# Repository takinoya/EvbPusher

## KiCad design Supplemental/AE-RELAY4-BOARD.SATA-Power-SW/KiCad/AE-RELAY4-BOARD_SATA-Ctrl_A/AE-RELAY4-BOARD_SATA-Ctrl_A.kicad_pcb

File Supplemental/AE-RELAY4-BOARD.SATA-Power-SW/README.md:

[English](README.md) | [Japanese](README.ja.md)
----

# SFX Power Complex

TBD
\(Original is here ==> [Japanese](README.ja.md)\)

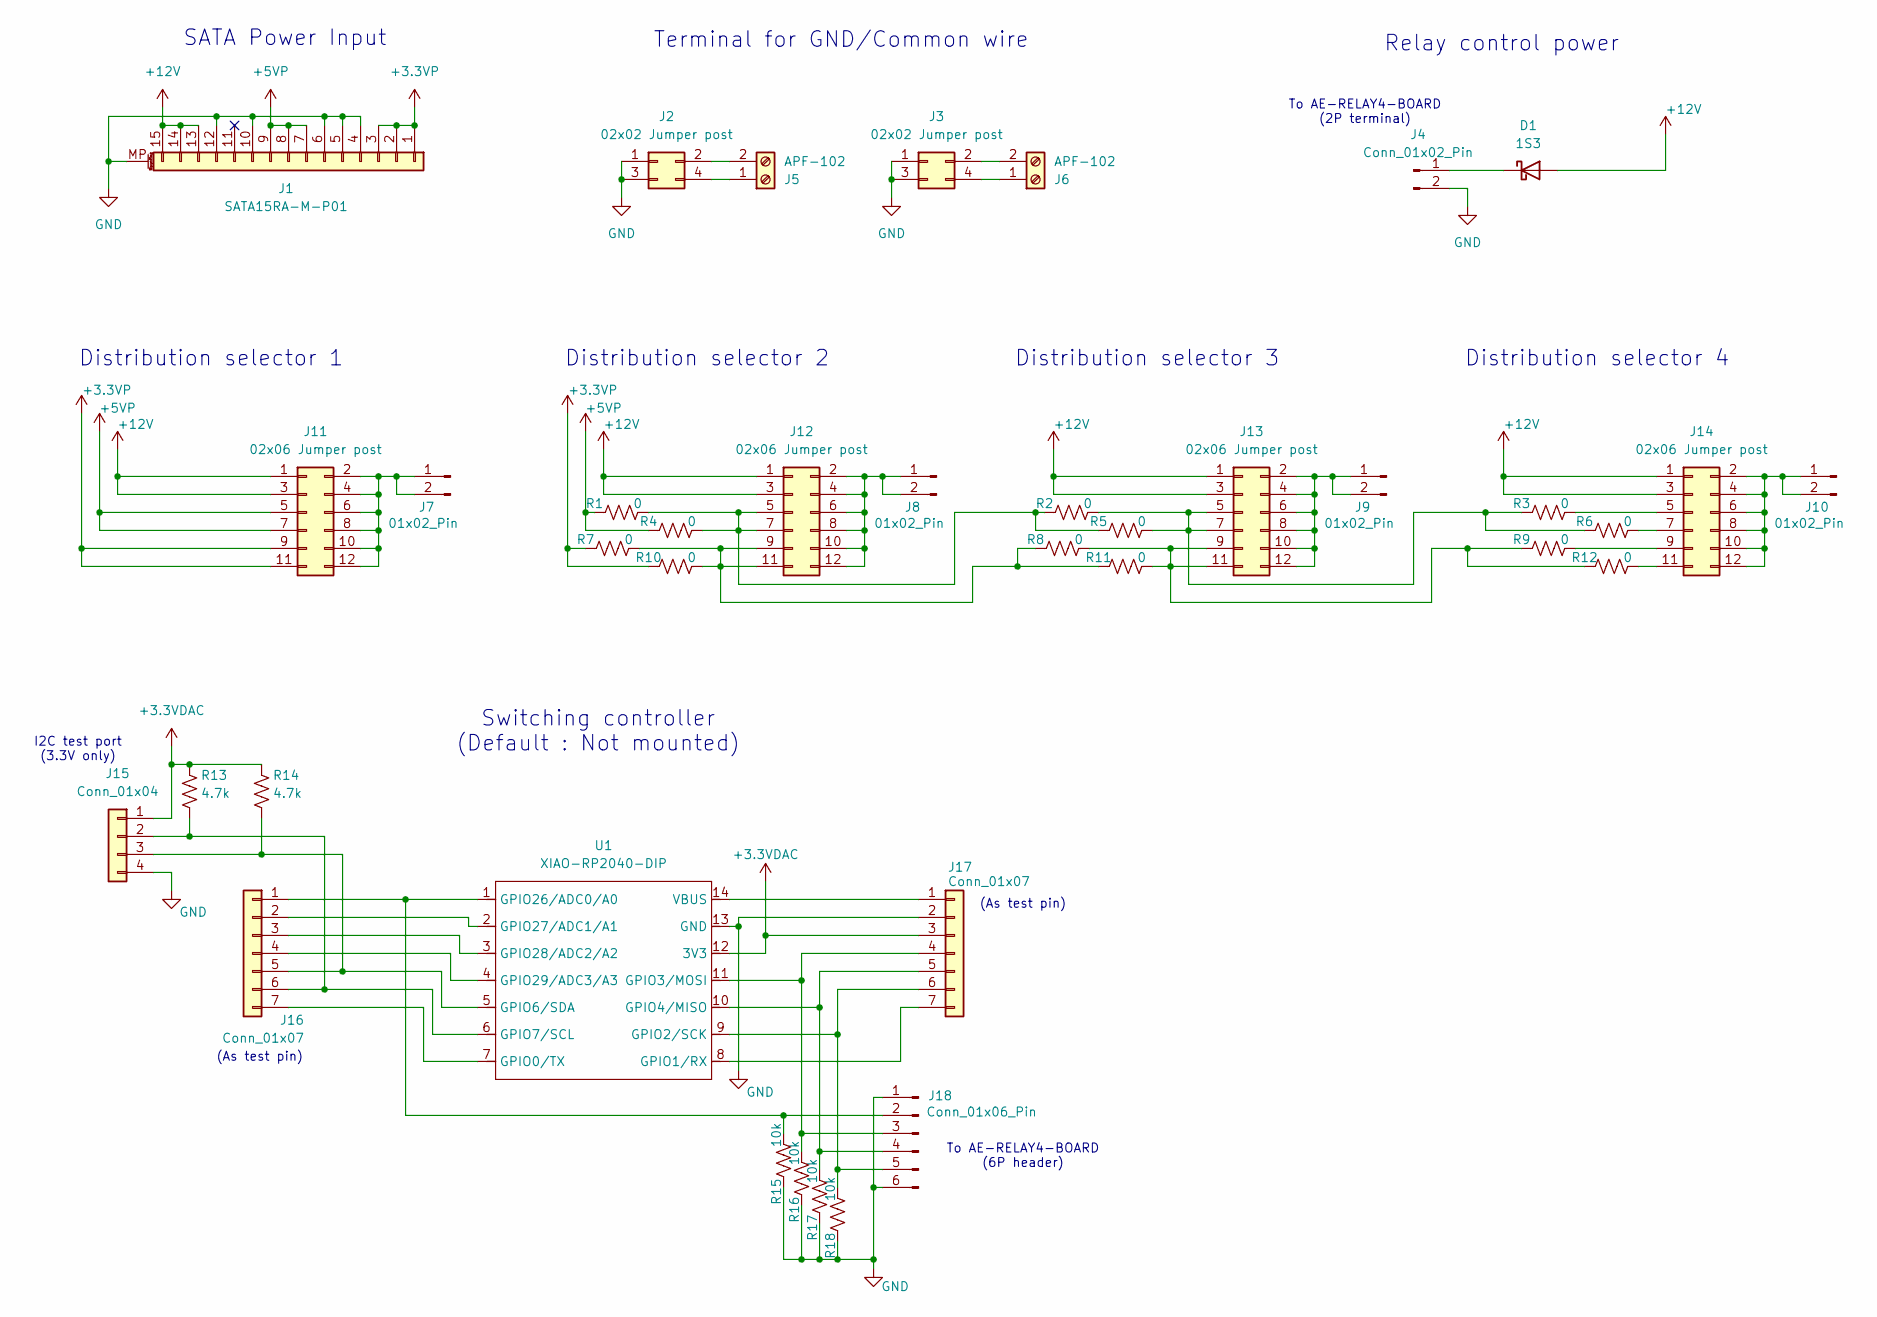
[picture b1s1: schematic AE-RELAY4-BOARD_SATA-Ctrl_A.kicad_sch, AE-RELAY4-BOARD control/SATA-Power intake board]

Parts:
D1: 1S3; D_DO-35_SOD27_P7.62mm_Horizontal
J1: SATA15RA-M-P01; SATA15RA-M-P01_Vertical_TOSA
J2, J3: 02x02 Jumper post; PinHeader_2x02_P2.54mm_nomargin_Vertical_TOSA
J4: Conn_01x02_Pin; PinHeader_1x02_P2.54mm_nomargin_Vertical_TOSA
J5, J6: APF-102; TerminalBlock_Phoenix_APF-102_1x02_P5.08mm_Horizontal
J7, J8, J9, J10: 01x02_Pin; PinHeader_1x02_P2.54mm_nomargin_Vertical_TOSA
J11, J12, J13, J14: 02x06 Jumper post; PinHeader_2x06_P2.54mm_nomargin_Vertical_TOSA
J15: Conn_01x04; PinHeader_1x04_P2.54mm_Vertical
J16, J17: Conn_01x07; PinHeader_1x07_P2.54mm_nomargin_Vertical_TOSA
J18: Conn_01x06_Pin; PinHeader_1x06_P2.54mm_Horizontal
R1, R2, R3, R4, R5, R6, R7, R8, R9, R10, R11, R12: 0; R_Axial_DIN0207_L6.3mm_D2.5mm_P10.16mm_Horizontal_TOSA
R13, R14: 4.7k; R_Axial_DIN0207_L6.3mm_D2.5mm_P2.54mm_Vertical_TOSA
R15, R16, R17, R18: 10k; R_Axial_DIN0207_L6.3mm_D2.5mm_P7.62mm_Horizontal_TOSA
U1: XIAO-RP2040-DIP

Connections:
+3.3VDAC: J15.1, J17.3, R13.1, R14.1, U1.12 (3V3)
+3.3VP: J1.1, J1.2, J1.3, J11.9, J11.11, R7.1, R10.1
+5VP: J1.7, J1.8, J1.9, J11.5, J11.7, R1.1, R4.1
+12V: D1.2 (A), J1.13, J1.14, J1.15, J11.1, J11.3, J12.1, J12.3, J13.1, J13.3, J14.1, J14.3
GND: J1.4, J1.5, J1.6, J1.10, J1.12, J1.MP (MountPin), J2.1, J2.3, J3.1, J3.3, J4.2, J15.4, J17.2, J18.1, J18.6, R15.2, R16.2, R17.2, R18.2, U1.13 (GND)
unnamed: D1.1 (K), J4.1
unnamed: J2.2, J5.2
unnamed: J2.4, J5.1
unnamed: J3.2, J6.2
unnamed: J3.4, J6.1
unnamed: J10.1, J10.2, J14.2, J14.4, J14.6, J14.8, J14.10, J14.12
unnamed: J7.1, J7.2, J11.2, J11.4, J11.6, J11.8, J11.10, J11.12
unnamed: J12.5, J12.7, R1.2, R2.1, R4.2, R5.1
unnamed: J8.1, J8.2, J12.2, J12.4, J12.6, J12.8, J12.10, J12.12
unnamed: J12.9, J12.11, R7.2, R8.1, R10.2, R11.1
unnamed: J13.5, J13.7, R2.2, R3.1, R5.2, R6.1
unnamed: J9.1, J9.2, J13.2, J13.4, J13.6, J13.8, J13.10, J13.12
unnamed: J13.9, J13.11, R8.2, R9.1, R11.2, R12.1
unnamed: J14.5, R3.2
unnamed: J14.7, R6.2
unnamed: J14.9, R9.2
unnamed: J14.11, R12.2
unnamed: J15.2, J16.6, R13.2, U1.6 (GPIO7/SCL)
unnamed: J15.3, J16.5, R14.2, U1.5 (GPIO6/SDA)
unnamed: J16.1, J18.2, R15.1, U1.1 (GPIO26/ADC0/A0)
unnamed: J16.2, U1.2 (GPIO27/ADC1/A1)
unnamed: J16.3, U1.3 (GPIO28/ADC2/A2)
unnamed: J16.4, U1.4 (GPIO29/ADC3/A3)
unnamed: J16.7, U1.7 (GPIO0/TX)
unnamed: J17.1, U1.14 (VBUS)
unnamed: J17.4, J18.3, R16.1, U1.11 (GPIO3/MOSI)
unnamed: J17.5, J18.4, R17.1, U1.10 (GPIO4/MISO)
unnamed: J17.6, J18.5, R18.1, U1.9 (GPIO2/SCK)
unnamed: J17.7, U1.8 (GPIO1/RX)

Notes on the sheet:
To AE-RELAY4-BOARD (6P header)
Distribution selector 4
Distribution selector 1
To AE-RELAY4-BOARD (2P terminal)
Relay control power
(As test pin)
Terminal for GND/Common wire
Switching controller (Default : Not mounted)
Distribution selector 2
Distribution selector 3
I2C test port (3.3V only)
SATA Power Input

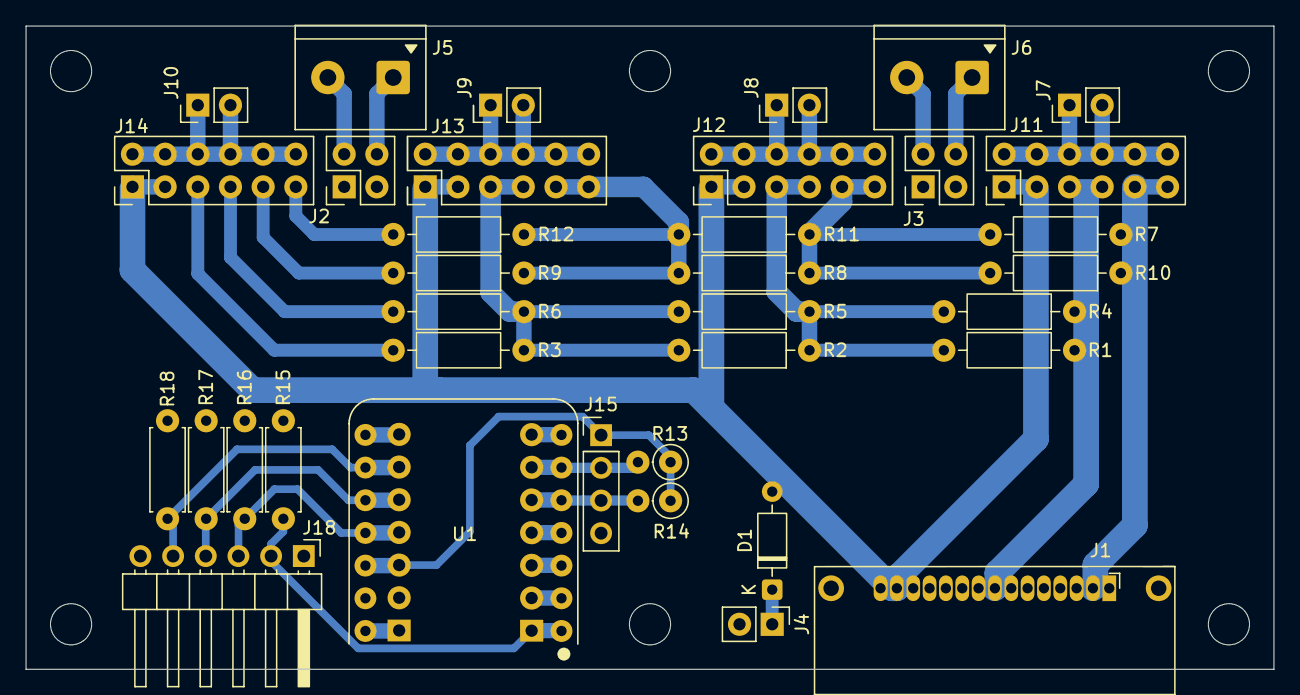
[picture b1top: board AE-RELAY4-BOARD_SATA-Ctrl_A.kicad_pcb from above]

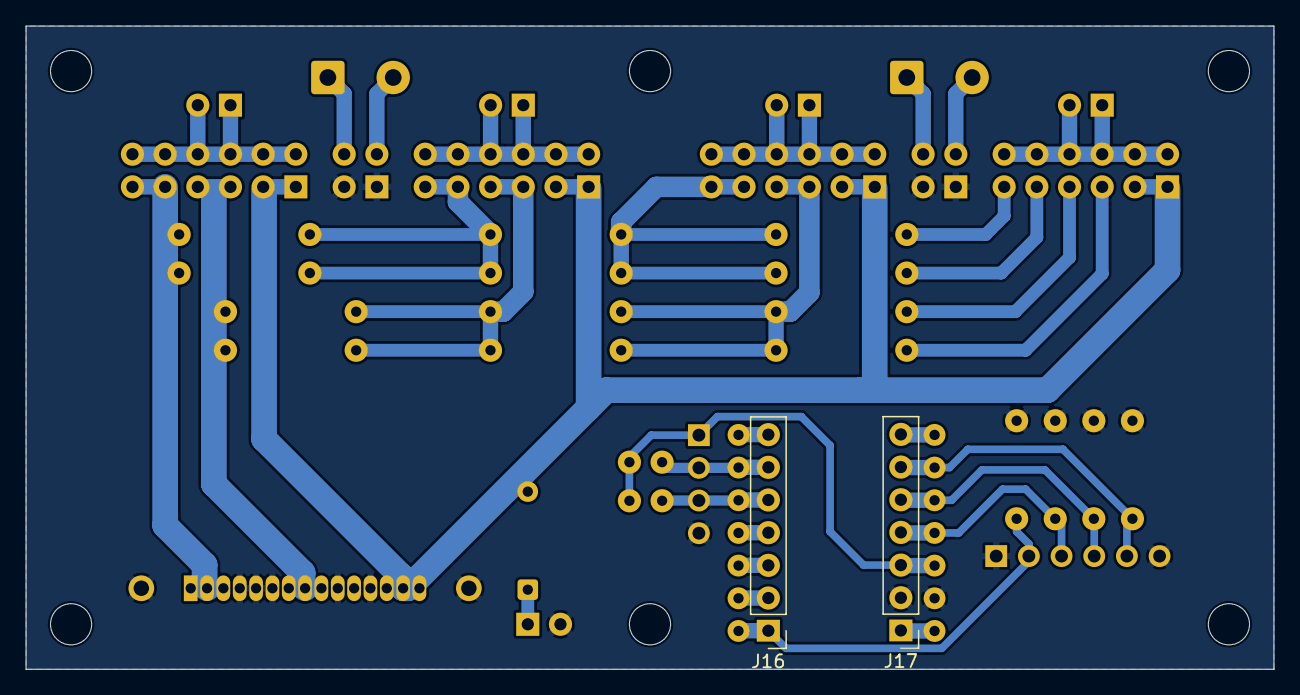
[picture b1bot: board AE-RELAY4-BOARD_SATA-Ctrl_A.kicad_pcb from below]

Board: 2 copper layers, 97.0 x 50.0 mm, 44 parts (2 on the bottom side), 34 nets.

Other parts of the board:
MH1, MH1#2, MH1#3, MH1#4, MH1#5, MH1#6: MountingHole_3.2mm_M3

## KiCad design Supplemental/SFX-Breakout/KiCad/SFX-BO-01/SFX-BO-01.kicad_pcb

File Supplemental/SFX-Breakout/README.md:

[English](README.md) | [Japanese](README.ja.md)
----

# SFX Breakout board

TBD
\(Original is here ==> [Japanese](README.ja.md)\)

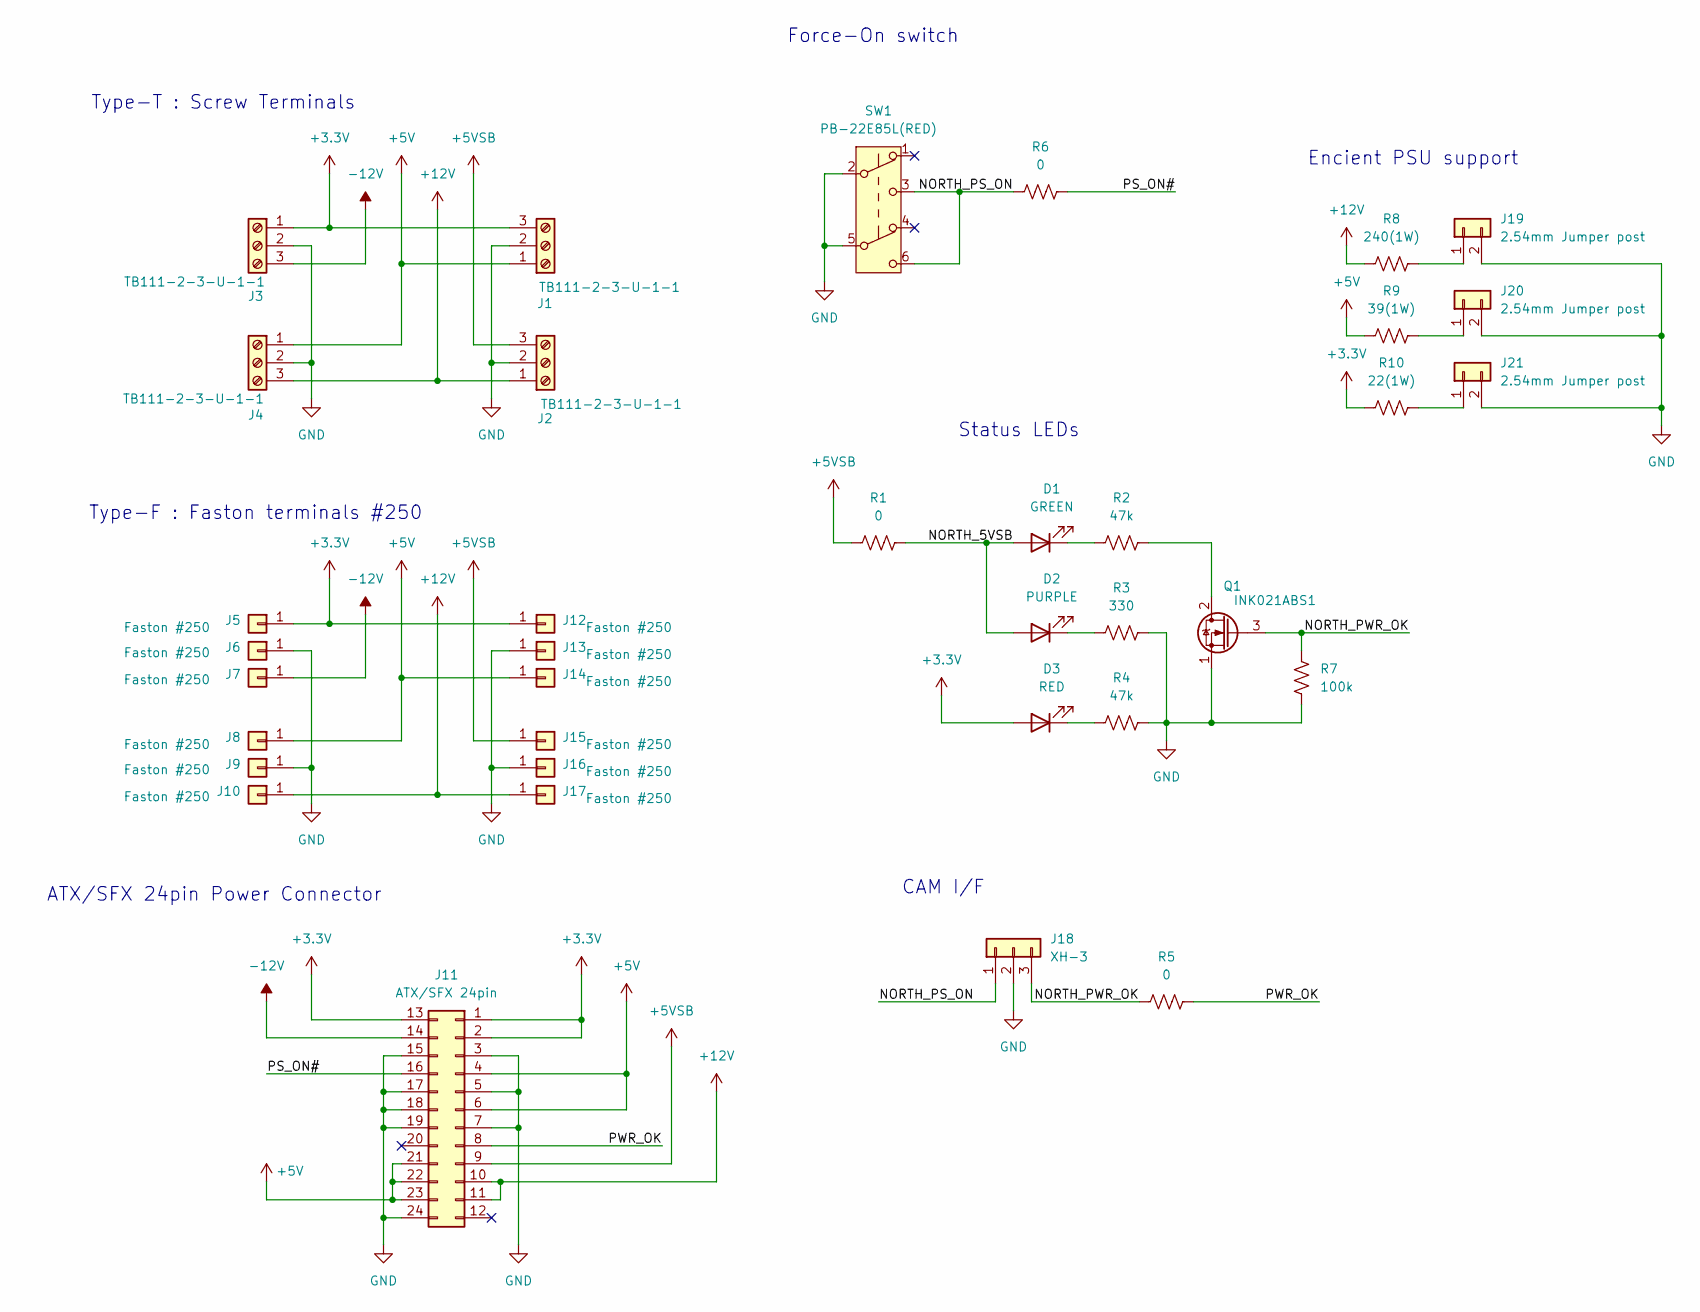
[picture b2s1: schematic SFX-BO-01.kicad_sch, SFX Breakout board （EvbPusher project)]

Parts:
D1: GREEN; LED_D3.0mm
D2: PURPLE; LED_D3.0mm
D3: RED; LED_D3.0mm
J1, J2, J3, J4: TB111-2-3-U-1-1; TerminalBlock_Alphaplus_TB111-2-3-U-1-1_1x03_P5.08mm_Horizo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
J5, J6, J7, J8, J9, J10, J12, J13, J14, J15, J16, J17: Faston #250; Faston_PC250
J11: ATX/SFX 24pin; Molex_Mini-Fit_Jr_5566-24A_2x12_P4.20mm_Vertical
J18: XH-3; JST_XH_B3B-XH-A_1x03_P2.50mm_Vertical
J19, J20, J21: 2.54mm Jumper post; PinHeader_1x02_P2.54mm_nomargin_Vertical
Q1: INK021ABS1; TO-92S_Wide_TMVC
R1, R5, R6: 0; R_Axial_DIN0207_L6.3mm_D2.5mm_P15.24mm_Horizontal_TOSA
R2, R4: 47k; R_Axial_DIN0207_L6.3mm_D2.5mm_P2.54mm_Vertical_TOSA
R3: 330; R_Axial_DIN0207_L6.3mm_D2.5mm_P2.54mm_Vertical_TOSA
R7: 100k; R_Axial_DIN0207_L6.3mm_D2.5mm_P2.54mm_Vertical_TOSA
R8: 240(1W); R_Axial_DIN0207_L6.3mm_D2.5mm_P2.54mm_Vertical_TOSA
R9: 39(1W); R_Axial_DIN0207_L6.3mm_D2.5mm_P2.54mm_Vertical_TOSA
R10: 22(1W); R_Axial_DIN0207_L6.3mm_D2.5mm_P2.54mm_Vertical_TOSA
SW1: PB-22E85L(RED); SW_Push_2P2T_Toggle_PB-22E85L

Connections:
+3.3V: D3.2 (A), J1.3, J3.1, J5.1, J11.1, J11.2, J11.13, J12.1, R10.1
+5V: J1.1, J4.1, J8.1, J11.4, J11.6, J11.21, J11.22, J11.23, J14.1, R9.1
+5VSB: J2.3, J11.9, J15.1, R1.1
+12V: J2.1, J4.3, J10.1, J11.10, J11.11, J17.1, R8.1
-12V: J3.3, J7.1, J11.14
/NORTH_5VSB: D1.2 (A), D2.2 (A), R1.2
/NORTH_PS_ON: J18.1, R6.1, SW1.3 (C), SW1.6 (C)
/NORTH_PWR_OK: J18.3, Q1.3 (G), R5.1, R7.2
/PS_ON#: J11.16, R6.2
/PWR_OK: J11.8, R5.2
GND: J1.2, J2.2, J3.2, J4.2, J6.1, J9.1, J11.3, J11.5, J11.7, J11.15, J11.17, J11.18, J11.19, J11.24, J13.1, J16.1, J18.2, J19.2, J20.2, J21.2, Q1.1 (S), R3.2, R4.2, R7.1, SW1.2 (B), SW1.5 (B)
unnamed: D1.1 (K), R2.1
unnamed: D2.1 (K), R3.1
unnamed: D3.1 (K), R4.1
unnamed: J19.1, R8.2
unnamed: J20.1, R9.2
unnamed: J21.1, R10.2
unnamed: Q1.2 (D), R2.2

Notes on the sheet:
Type-T : Screw Terminals
CAM I/F
ATX/SFX 24pin Power Connector
Status LEDs
Encient PSU support
Type-F : Faston terminals #250
Force-On switch

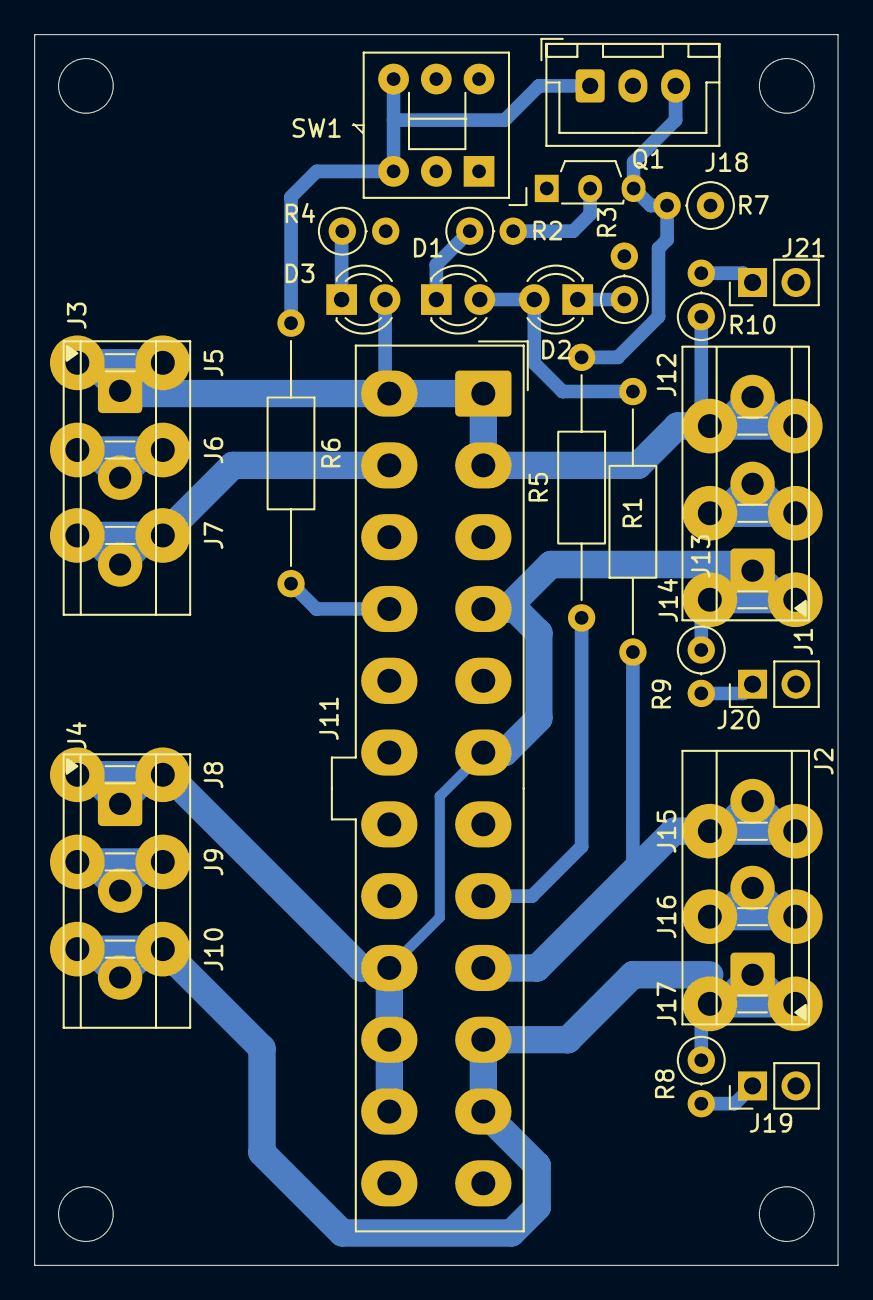
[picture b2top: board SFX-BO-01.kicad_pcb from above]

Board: 2 copper layers, 47.0 x 72.0 mm, 40 parts (0 on the bottom side), 18 nets.

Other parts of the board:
MH1, MH2, MH3, MH4: MountingHole_3.2mm_M3

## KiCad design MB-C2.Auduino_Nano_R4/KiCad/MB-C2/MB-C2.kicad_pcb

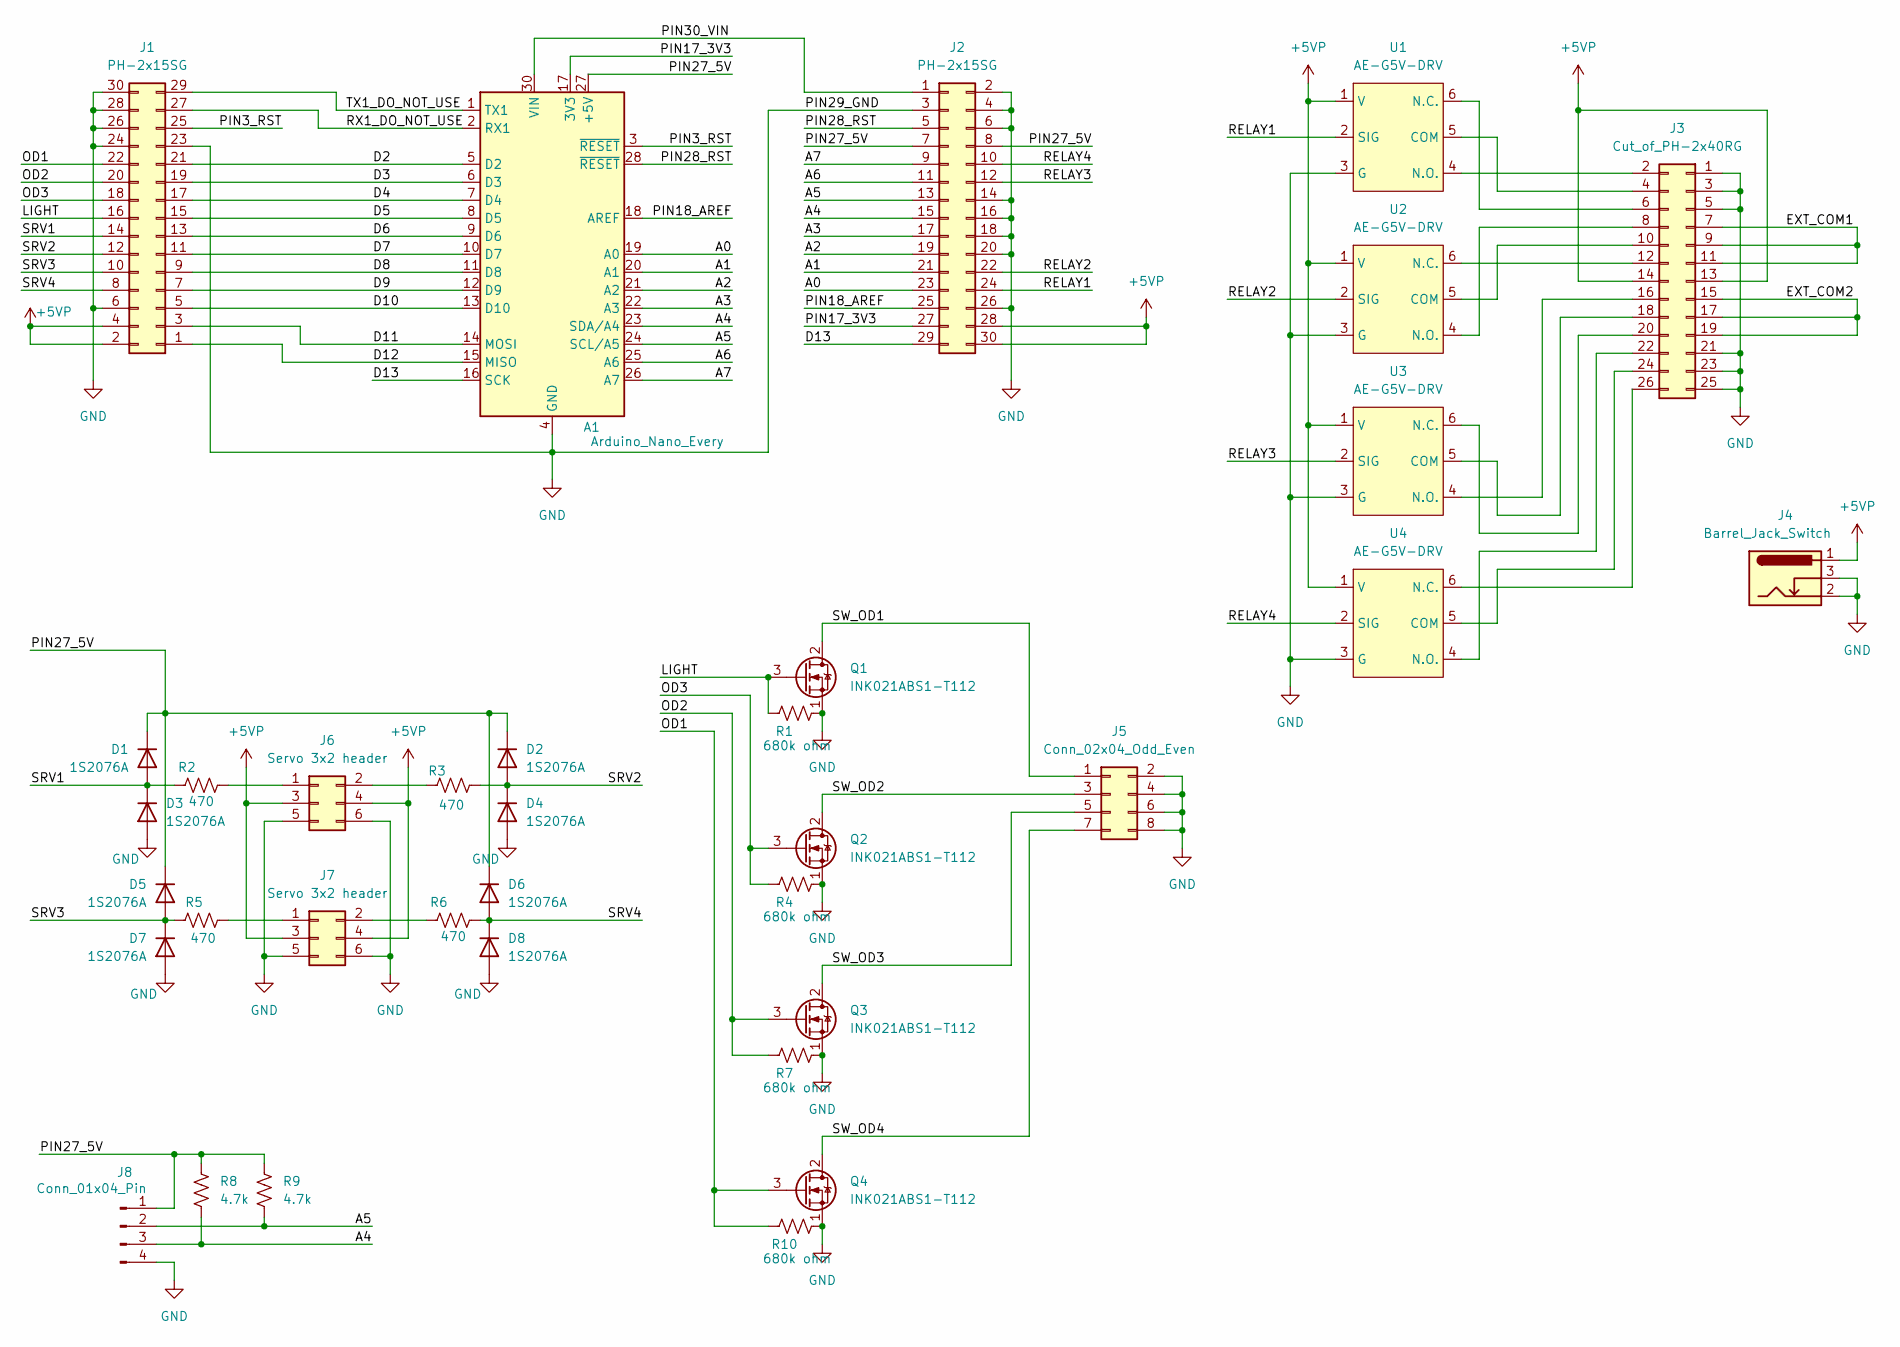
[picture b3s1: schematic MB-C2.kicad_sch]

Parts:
A1: Arduino_Nano_Every; Arduino_Nano__silk_tune
D1, D2, D3, D4, D5, D6, D7, D8: 1S2076A; D_DO-34_SOD68_P2.54mm_Vertical_KathodeUp
J1, J2: PH-2x15SG; PinHeader_2x15_P2.54mm_Vertical
J3: Cut_of_PH-2x40RG; PinHeader_2x13_P2.54mm_Vertical
J4: Barrel_Jack_Switch; BarrelJack_2.1mm_4A_18742_TMVC
J5: Conn_02x04_Odd_Even; PinHeader_2x04_P2.54mm_nomargin_Vertical
J6, J7: Servo 3x2 header; PinHeader_2x03_P2.54mm_nomargin_Vertical
J8: Conn_01x04_Pin; PinHeader_1x04_P2.54mm_Vertical
Q1, Q2, Q3, Q4: INK021ABS1-T112; TO-92S_Wide_TMVC
R1, R4, R7, R10: 680k ohm; R_Axial_DIN0204_L3.6mm_D1.6mm_P2.54mm_Vertical
R2, R5: 470; R_Axial_DIN0204_L3.6mm_D1.6mm_P5.08mm_Horizontal
R3, R6: 470; R_Axial_DIN0204_L3.6mm_D1.6mm_P2.54mm_Vertical
R8, R9: 4.7k; R_Axial_DIN0204_L3.6mm_D1.6mm_P7.62mm_Horizontal_TMVC
U1, U2, U3, U4: AE-G5V-DRV

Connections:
+5VP: J1.2, J1.4, J2.28, J2.30, J3.13, J3.14, J4.1, J6.3, J6.4, J7.3, J7.4, U1.1 (V), U2.1 (V), U3.1 (V), U4.1 (V)
/A0: A1.19 (A0), J2.23
/A1: A1.20 (A1), J2.21
/A2: A1.21 (A2), J2.19
/A3: A1.22 (A3), J2.17
/A4: A1.23 (SDA/A4), J2.15, J8.3, R8.2
/A5: A1.24 (SCL/A5), J2.13, J8.2, R9.2
/A6: A1.25 (A6), J2.11
/A7: A1.26 (A7), J2.9
/D2: A1.5 (D2), J1.21
/D3: A1.6 (D3), J1.19
/D4: A1.7 (D4), J1.17
/D5: A1.8 (D5), J1.15
/D6: A1.9 (D6), J1.13
/D7: A1.10 (D7), J1.11
/D8: A1.11 (D8), J1.9
/D9: A1.12 (D9), J1.7
/D10: A1.13 (D10), J1.5
/D11: A1.14 (MOSI), J1.3
/D12: A1.15 (MISO), J1.1
/D13: A1.16 (SCK), J2.29
/EXT_COM1: J3.7, J3.9, J3.11
/EXT_COM2: J3.15, J3.17, J3.19
/LIGHT: J1.16, Q1.3 (G), R1.1
/OD1: J1.22, Q4.3 (G), R10.1
/OD2: J1.20, Q3.3 (G), R7.1
/OD3: J1.18, Q2.3 (G), R4.1
/PIN3_RST: A1.3 (~RESET), J1.25
/PIN17_3V3: A1.17 (3V3), J2.27
/PIN18_AREF: A1.18 (AREF), J2.25
/PIN27_5V: A1.27 (+5V), D1.1 (K), D2.1 (K), D5.1 (K), D6.1 (K), J2.7, J2.8, J8.1, R8.1, R9.1
/PIN28_RST: A1.28 (~RESET), J2.5
/PIN30_VIN: A1.30 (VIN), J2.1
/RELAY1: J2.24, U1.2 (SIG)
/RELAY2: J2.22, U2.2 (SIG)
/RELAY3: J2.12, U3.2 (SIG)
/RELAY4: J2.10, U4.2 (SIG)
/RX1_DO_NOT_USE: A1.2 (RX1), J1.27
/SRV1: D1.2 (A), D3.1 (K), J1.14, R2.1
/SRV2: D2.2 (A), D4.1 (K), J1.12, R3.2
/SRV3: D5.2 (A), D7.1 (K), J1.10, R5.1
/SRV4: D6.2 (A), D8.1 (K), J1.8, R6.2
/SW_OD1: J5.1, Q1.2 (D)
/SW_OD2: J5.3, Q2.2 (D)
/SW_OD3: J5.5, Q3.2 (D)
/SW_OD4: J5.7, Q4.2 (D)
/TX1_DO_NOT_USE: A1.1 (TX1), J1.29
GND: A1.4 (GND), A1.29 (GND), D3.2 (A), D4.2 (A), D7.2 (A), D8.2 (A), J1.6, J1.23, J1.24, J1.26, J1.28, J1.30, J2.2, J2.3, J2.4, J2.6, J2.14, J2.16, J2.18, J2.20, J2.26, J3.1, J3.3, J3.5, J3.21, J3.23, J3.25, J4.2, J4.3, J5.2, J5.4, J5.6, J5.8, J6.5, J6.6, J7.5, J7.6, J8.4, Q1.1 (S), Q2.1 (S), Q3.1 (S), Q4.1 (S), R1.2, R4.2, R7.2, R10.2, U1.3 (G), U2.3 (G), U3.3 (G), U4.3 (G)
unnamed: J3.2, U1.4 (N.O.)
unnamed: J3.4, U1.5 (COM)
unnamed: J3.6, U1.6 (N.C.)
unnamed: J3.8, U2.4 (N.O.)
unnamed: J3.10, U2.5 (COM)
unnamed: J3.12, U2.6 (N.C.)
unnamed: J3.16, U3.4 (N.O.)
unnamed: J3.18, U3.5 (COM)
unnamed: J3.20, U3.6 (N.C.)
unnamed: J3.22, U4.4 (N.O.)
unnamed: J3.24, U4.5 (COM)
unnamed: J3.26, U4.6 (N.C.)
unnamed: J6.1, R2.2
unnamed: J6.2, R3.1
unnamed: J7.1, R5.2
unnamed: J7.2, R6.1

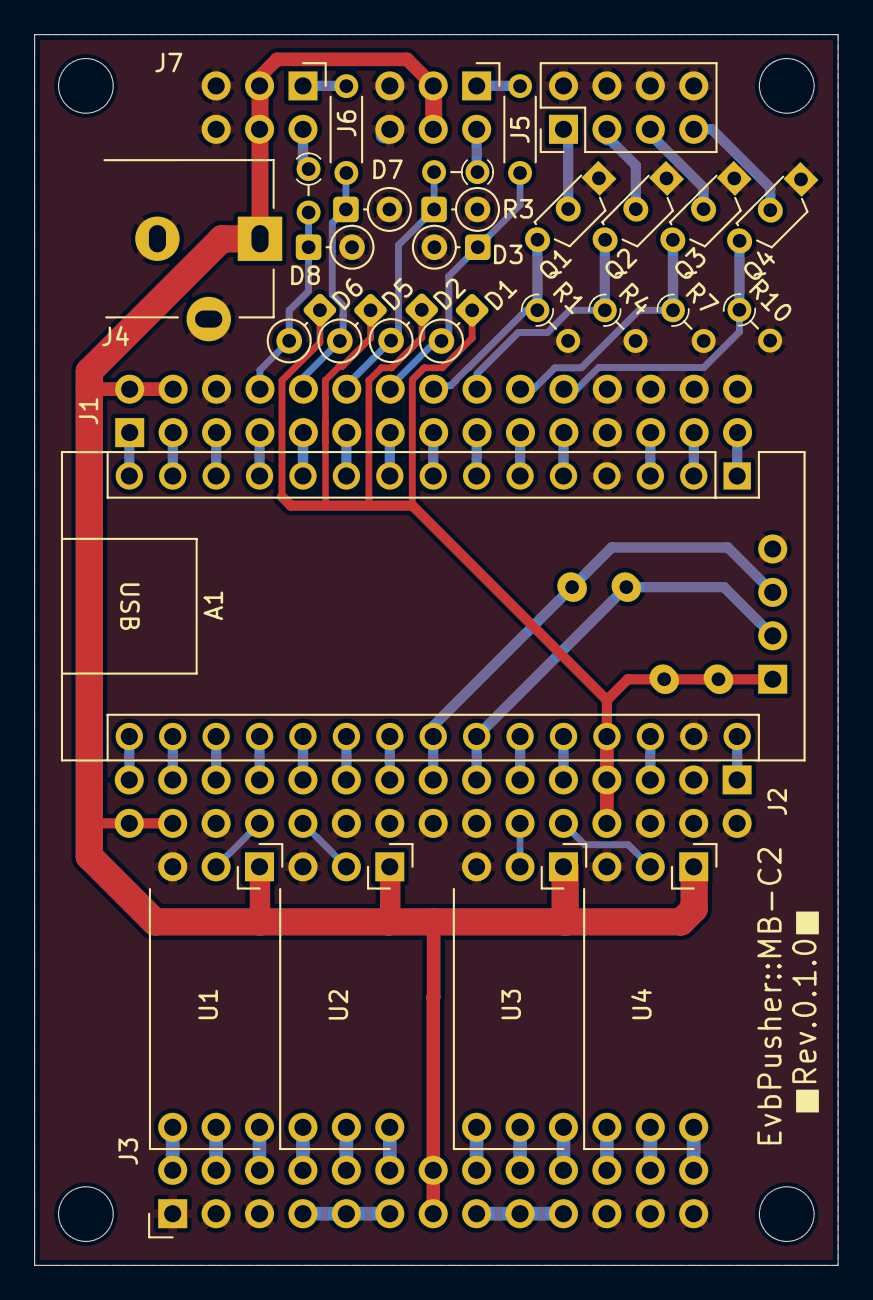
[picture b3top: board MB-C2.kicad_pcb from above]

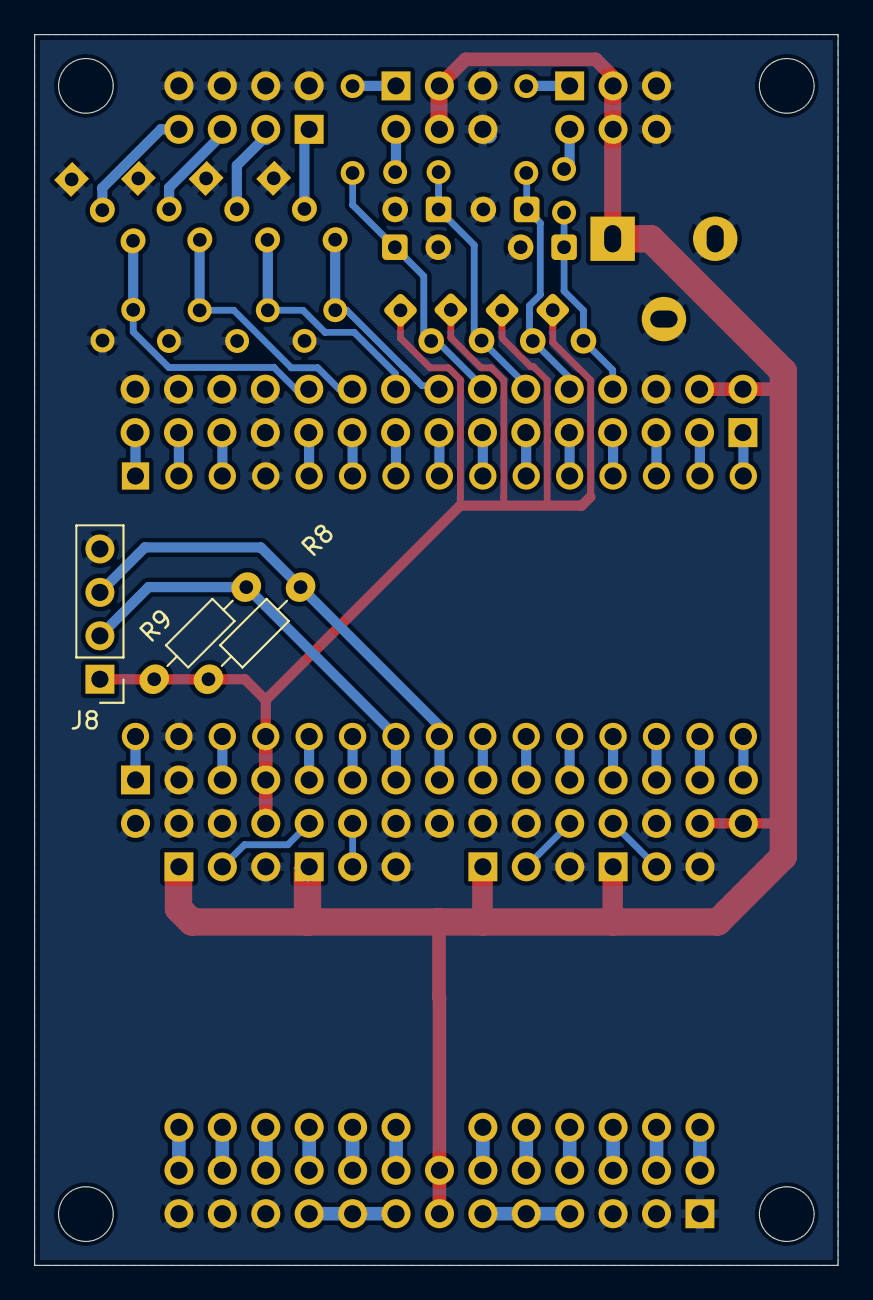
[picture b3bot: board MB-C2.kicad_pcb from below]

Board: 2 copper layers, 47.0 x 72.0 mm, 39 parts (3 on the bottom side), 64 nets.

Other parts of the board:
MH1, MH2, MH3, MH4: MountingHole_3.2mm_M3

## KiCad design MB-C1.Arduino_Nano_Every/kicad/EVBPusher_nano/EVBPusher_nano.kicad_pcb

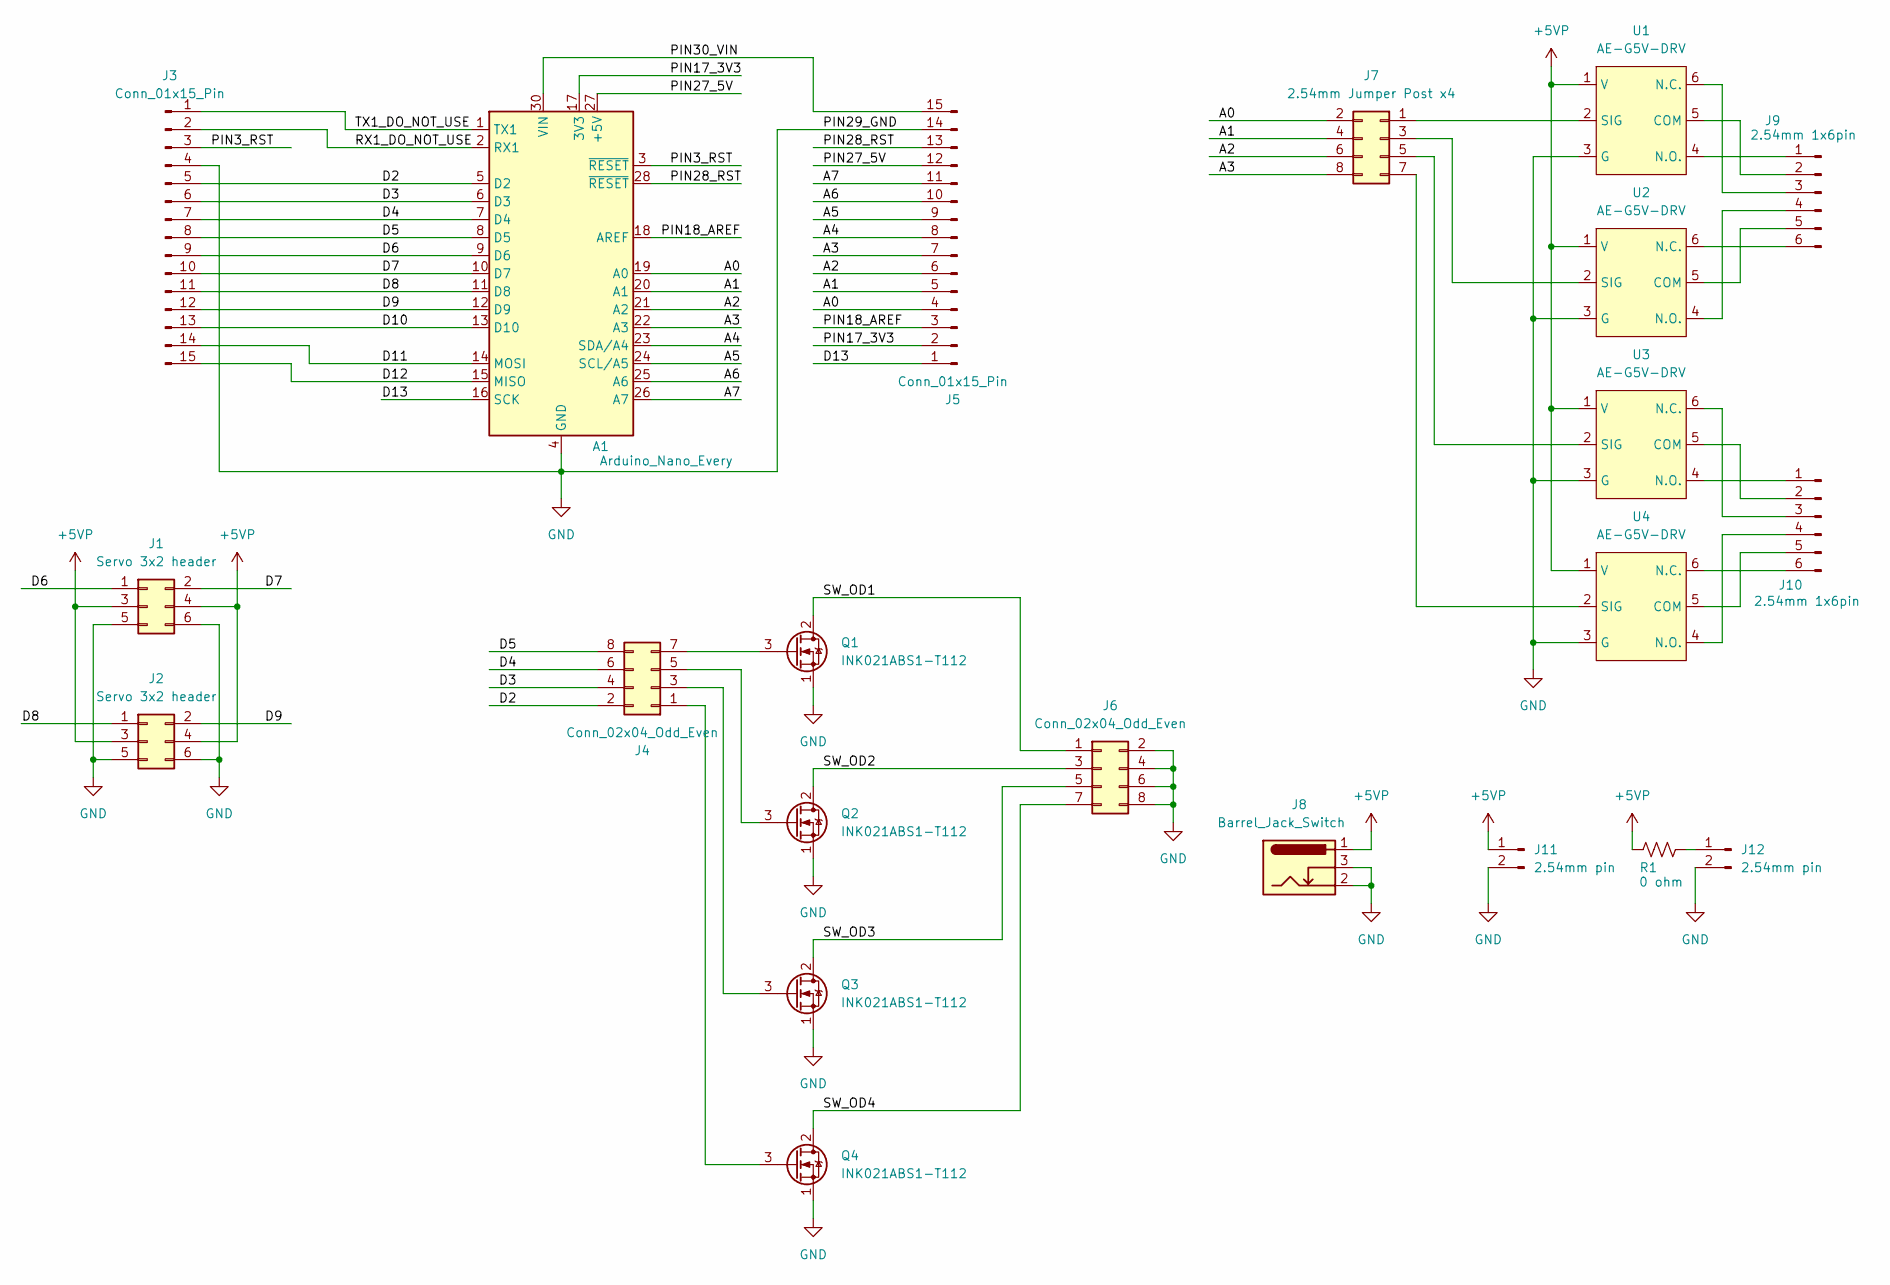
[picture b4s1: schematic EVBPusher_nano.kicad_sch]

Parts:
A1: Arduino_Nano_Every; Arduino_Nano
J1, J2: Servo 3x2 header; PinHeader_2x03_P2.54mm_nomargin_Vertical
J3, J5: Conn_01x15_Pin; PinHeader_1x15_P2.54mm_nomargein_Vertical
J4, J6: Conn_02x04_Odd_Even; PinHeader_2x04_P2.54mm_nomargin_Vertical
J7: 2.54mm Jumper Post x4; PinHeader_2x04_P2.54mm_nomargin_Vertical
J8: Barrel_Jack_Switch; BarrelJack_2.1mm_4A_18742_TMVC
J9, J10: 2.54mm 1x6pin; PinHeader_1x06_P2.54mm_nomargin_Vertical
J11, J12: 2.54mm pin; PinHeader_1x02_P2.54mm_nomargin_Vertical
Q1, Q2, Q3, Q4: INK021ABS1-T112; TO-92S_Wide_TMVC
R1: 0 ohm; R_Axial_DIN0204_L3.6mm_D1.6mm_P7.62mm_Horizontal_TMVC
U1, U2, U3, U4: AE-G5V-DRV

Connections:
+5VP: J1.3, J1.4, J2.3, J2.4, J8.1, J11.1, R1.1, U1.1 (V), U2.1 (V), U3.1 (V), U4.1 (V)
/A0: A1.19 (A0), J5.4, J7.2
/A1: A1.20 (A1), J5.5, J7.4
/A2: A1.21 (A2), J5.6, J7.6
/A3: A1.22 (A3), J5.7, J7.8
/A4: A1.23 (SDA/A4), J5.8
/A5: A1.24 (SCL/A5), J5.9
/A6: A1.25 (A6), J5.10
/A7: A1.26 (A7), J5.11
/D2: A1.5 (D2), J3.5, J4.2
/D3: A1.6 (D3), J3.6, J4.4
/D4: A1.7 (D4), J3.7, J4.6
/D5: A1.8 (D5), J3.8, J4.8
/D6: A1.9 (D6), J1.1, J3.9
/D7: A1.10 (D7), J1.2, J3.10
/D8: A1.11 (D8), J2.1, J3.11
/D9: A1.12 (D9), J2.2, J3.12
/D10: A1.13 (D10), J3.13
/D11: A1.14 (MOSI), J3.14
/D12: A1.15 (MISO), J3.15
/D13: A1.16 (SCK), J5.1
/PIN3_RST: A1.3 (~RESET), J3.3
/PIN17_3V3: A1.17 (3V3), J5.2
/PIN18_AREF: A1.18 (AREF), J5.3
/PIN27_5V: A1.27 (+5V), J5.12
/PIN28_RST: A1.28 (~RESET), J5.13
/PIN30_VIN: A1.30 (VIN), J5.15
/RX1_DO_NOT_USE: A1.2 (RX1), J3.2
/SW_OD1: J6.1, Q1.2 (D)
/SW_OD2: J6.3, Q2.2 (D)
/SW_OD3: J6.5, Q3.2 (D)
/SW_OD4: J6.7, Q4.2 (D)
/TX1_DO_NOT_USE: A1.1 (TX1), J3.1
GND: A1.4 (GND), A1.29 (GND), J1.5, J1.6, J2.5, J2.6, J3.4, J5.14, J6.2, J6.4, J6.6, J6.8, J8.2, J8.3, J11.2, J12.2, Q1.1 (S), Q2.1 (S), Q3.1 (S), Q4.1 (S), U1.3 (G), U2.3 (G), U3.3 (G), U4.3 (G)
unnamed: J4.1, Q4.3 (G)
unnamed: J4.3, Q3.3 (G)
unnamed: J4.5, Q2.3 (G)
unnamed: J4.7, Q1.3 (G)
unnamed: J7.1, U1.2 (SIG)
unnamed: J7.3, U2.2 (SIG)
unnamed: J7.5, U3.2 (SIG)
unnamed: J7.7, U4.2 (SIG)
unnamed: J9.1, U1.4 (N.O.)
unnamed: J9.2, U1.5 (COM)
unnamed: J9.3, U1.6 (N.C.)
unnamed: J9.4, U2.4 (N.O.)
unnamed: J9.5, U2.5 (COM)
unnamed: J9.6, U2.6 (N.C.)
unnamed: J10.1, U3.4 (N.O.)
unnamed: J10.2, U3.5 (COM)
unnamed: J10.3, U3.6 (N.C.)
unnamed: J10.4, U4.4 (N.O.)
unnamed: J10.5, U4.5 (COM)
unnamed: J10.6, U4.6 (N.C.)
unnamed: J12.1, R1.2

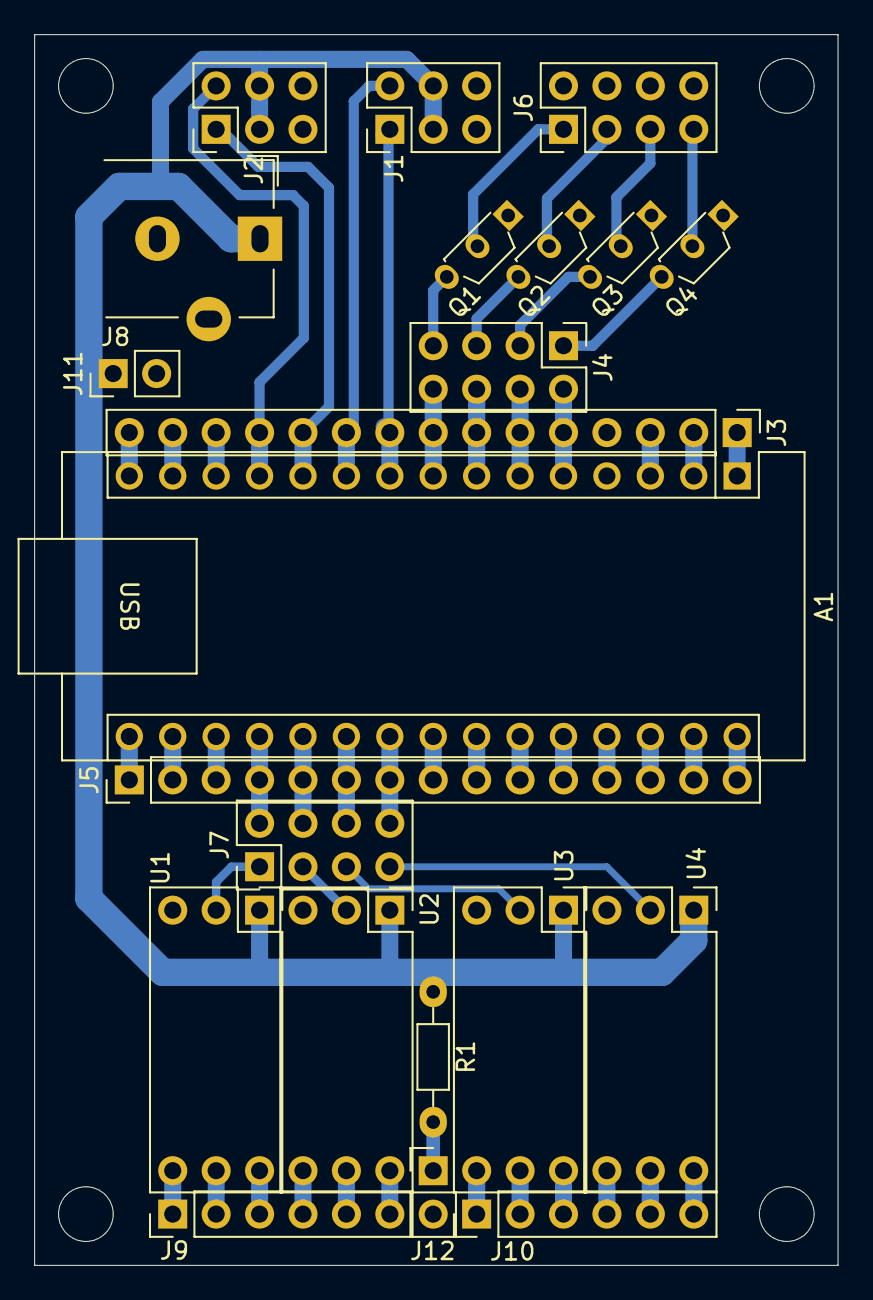
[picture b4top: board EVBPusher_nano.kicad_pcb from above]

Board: 2 copper layers, 47.0 x 72.0 mm, 26 parts (0 on the bottom side), 55 nets.

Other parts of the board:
MH1, MH2, MH3, MH4: MountingHole_3.2mm_M3
